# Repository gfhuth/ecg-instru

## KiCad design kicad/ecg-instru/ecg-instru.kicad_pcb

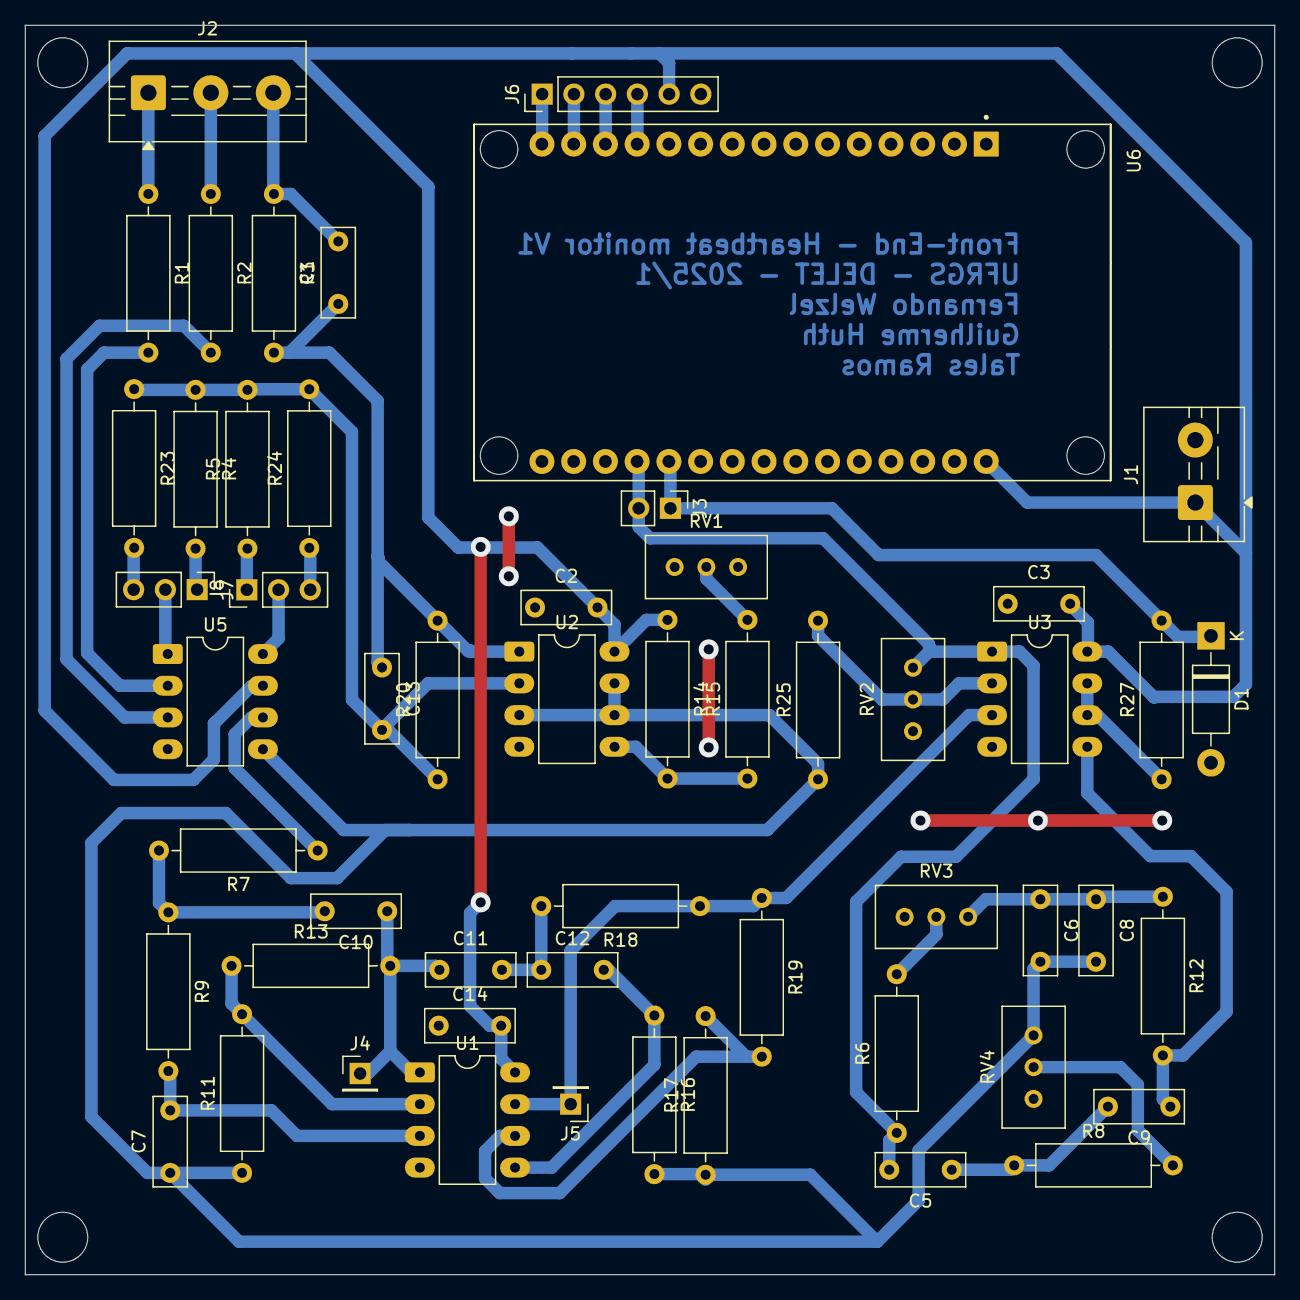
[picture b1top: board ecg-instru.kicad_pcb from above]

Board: 2 copper layers, 100.0 x 100.0 mm, 54 parts (0 on the bottom side), 40 nets.

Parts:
C1, C13: 12n; C_Rect_L7.0mm_W2.5mm_P5.00mm
C2, C3, C14: 100n; C_Rect_L7.0mm_W2.5mm_P5.00mm
C5, C6, C8, C9: 47n; C_Rect_L7.0mm_W2.5mm_P5.00mm
C7, C10: 22n; C_Rect_L7.0mm_W2.5mm_P5.00mm
C11, C12: 220n; C_Rect_L7.0mm_W2.5mm_P5.00mm
D1: 3V3; D_DO-41_SOD81_P10.16mm_Horizontal
J1: Screw_Terminal_01x02; TerminalBlock_MaiXu_MX126-5.0-02P_1x02_P5.00mm
J2: Screw_Terminal_01x03; TerminalBlock_MaiXu_MX126-5.0-03P_1x03_P5.00mm
J3: Conn_01x02_Socket; PinHeader_1x02_P2.54mm_Vertical
J4, J5: Conn_01x01_Socket; PinHeader_1x01_P2.54mm_Vertical
J6: Conn_01x06_Socket; PinHeader_1x06_P2.54mm_Vertical
J7, J8: Conn_01x03_Socket; PinHeader_1x03_P2.54mm_Vertical
R1, R2, R3, R20: 220k; R_Axial_DIN0309_L9.0mm_D3.2mm_P12.70mm_Horizontal
R4, R5, R25, R27: 1k; R_Axial_DIN0309_L9.0mm_D3.2mm_P12.70mm_Horizontal
R6, R12: 56k; R_Axial_DIN0309_L9.0mm_D3.2mm_P12.70mm_Horizontal
R7, R9: 180k; R_Axial_DIN0309_L9.0mm_D3.2mm_P12.70mm_Horizontal
R8: 27k; R_Axial_DIN0309_L9.0mm_D3.2mm_P12.70mm_Horizontal
R11, R13, R17, R19: 10k; R_Axial_DIN0309_L9.0mm_D3.2mm_P12.70mm_Horizontal
R14: 5k6; R_Axial_DIN0309_L9.0mm_D3.2mm_P12.70mm_Horizontal
R15: 2k2; R_Axial_DIN0309_L9.0mm_D3.2mm_P12.70mm_Horizontal
R16, R18: 1M5; R_Axial_DIN0309_L9.0mm_D3.2mm_P12.70mm_Horizontal
R23, R24: 12k; R_Axial_DIN0309_L9.0mm_D3.2mm_P12.70mm_Horizontal
RV1, RV3: 1k; Potentiometer_Bourns_3296W_Vertical
RV2: 10k; Potentiometer_Bourns_3296W_Vertical
RV4: 2k; Potentiometer_Bourns_3296W_Vertical
U1, U2, U3: LM358; DIP-8_W7.62mm_LongPads
U5: INA114; DIP-8_W7.62mm_LongPads
U6: ESP32-DEVKIT-V1; MODULE_ESP32_DEVKIT_V1

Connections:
0: C2.1, C3.1, C14.1, D1.2 (A), J1.2, J6.6, RV1.1, U1.4 (V-), U2.4 (V-), U3.4 (V-), U5.4 (V-), U6.2 (GND), U6.29 (GND)
+5V: C2.2, C3.2, C14.2, J1.1, J6.5, R14.1, U1.8 (V+), U2.8 (V+), U3.8 (V+), U5.7 (V+), U6.30 (VIN)
B0: J6.2, U6.14 (D22)
B1: J6.1, U6.15 (D23)
COM: C13.2, R4.1, R5.2, R20.1, R23.1, R24.2, U2.2 (-)
GNDREF: C6.2, C7.1, C8.2, R11.1, R16.2, R17.1, R25.1, RV4.1, U2.3 (+), U2.6 (-), U2.7, U5.5 (Ref)
I2C1_SCL: J6.3, U6.13 (TX0)
I2C1_SDA: J6.4, U6.12 (RX0)
LA: R1.2, U5.2 (-)
LA_E: J2.1, R1.1
unnamed: C5.1, C9.2, R8.1
unnamed: C6.1, C8.1, R12.1, RV3.1
unnamed: C10.2, R7.2, R9.1
unnamed: C11.2, C12.1, R18.2
unnamed: C10.1, C11.1, J4.1, R13.2, U1.1
unnamed: J5.1, R18.1, R19.1, U1.7, U3.3 (+)
unnamed: J7.1, R4.2
unnamed: J7.2, U5.1 (Rg)
unnamed: J7.3, R23.2
unnamed: J8.1, R5.1
unnamed: J8.2, U5.8 (Rg)
unnamed: J8.3, R24.1
unnamed: R6.2, RV3.2
unnamed: R8.2, RV4.2
unnamed: R15.2, RV1.2
unnamed: C7.2, R9.2, U1.3 (+)
unnamed: R11.2, R13.1, U1.2 (-)
unnamed: C12.2, R16.1, U1.5 (+)
unnamed: R17.2, R19.2, U1.6 (-)
unnamed: R14.2, R15.1, U2.5 (+)
unnamed: R25.2, RV2.2, U3.2 (-)
unnamed: C9.1, R12.2, U3.5 (+)
unnamed: R27.1, U3.6 (-), U3.7
RA: R2.2, U5.3 (+)
RA_E: J2.2, R2.1
RL: C1.1, C13.1, R3.2, R20.2, U2.1
RL_E: C1.2, J2.3, R3.1
VADC: D1.1 (K), J3.1, R27.2, U6.20 (D35)
VINA: R7.1, U5.6
VSENSE: C5.2, J3.2, R6.1, RV2.1, U3.1, U6.19 (D34)

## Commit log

2025-06-16 First schematic version
2025-06-21 New schematic with correct components
2025-06-29 Board layout + Schematic + ESP32 initial src
2025-07-02 bpm, download csv and time sync
2025-07-02 platformio
2025-07-04 Fixing stream buffer and time on csv
2025-07-05 reimplementei
2025-07-05 serial plotter
2025-07-05 sem debug
2025-07-06 funcionando 500hz
2025-07-09 inicio do plotter clonado
2025-07-09 ignora mudancas no arquivo de credenciais wifi
2025-07-09 funcionando para platformio
2025-07-09 Aquisição dos dados no navegador com sucesso.
2025-07-10 Filtragem funcionando
